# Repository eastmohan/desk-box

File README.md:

# desk-box
box on my desk with clock, timer/pomodoro timer, alarm clock, stop watch, maybe also make it a bluetooth speaker idk. havent decided if battery powered or plug in. i might also add charging ports for it to charge stuff like my phone. lamp too.

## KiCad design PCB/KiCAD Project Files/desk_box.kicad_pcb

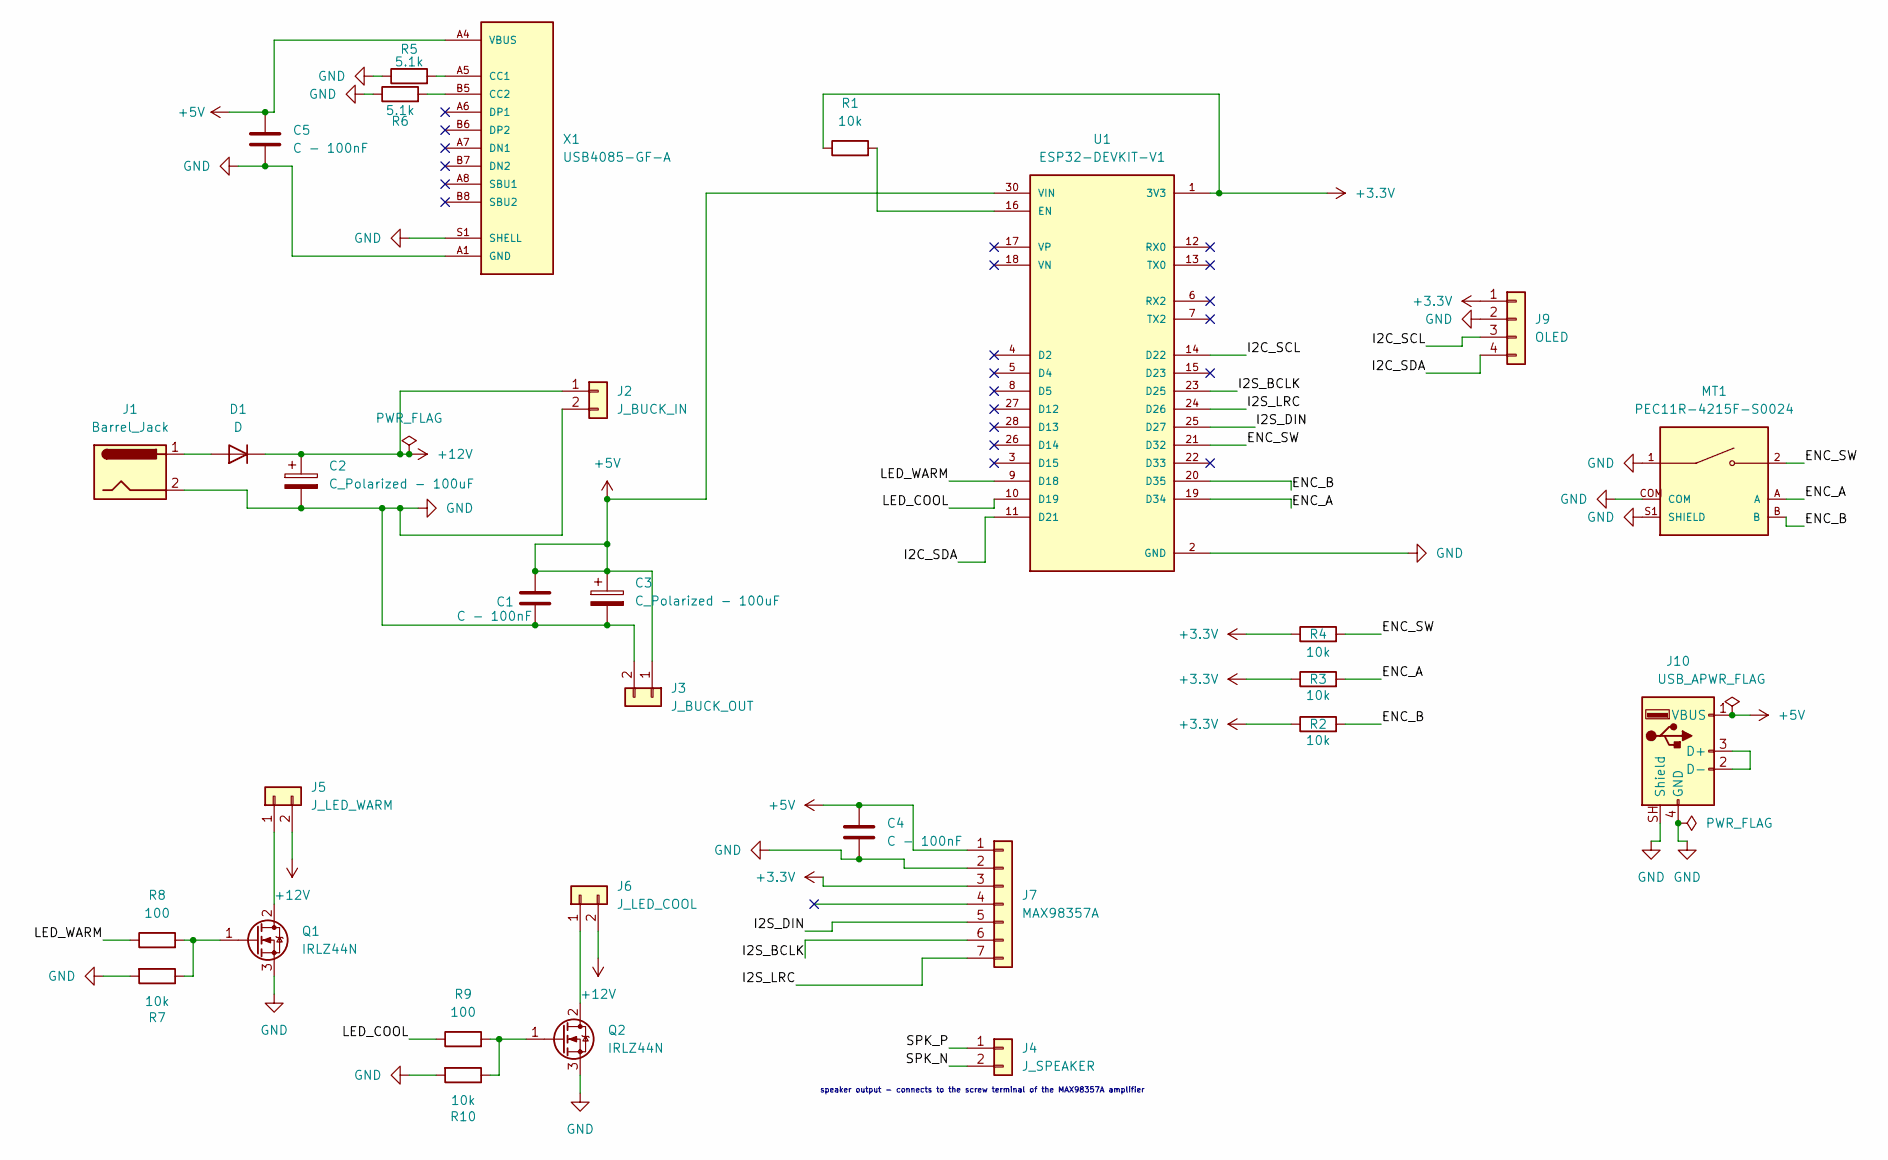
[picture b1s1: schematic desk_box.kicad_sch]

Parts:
C1, C4, C5: C - 100nF; C_Disc_D5.0mm_W2.5mm_P5.00mm
C2, C3: C_Polarized - 100uF; CP_Radial_D8.0mm_P3.50mm
D1: D; D_DO-41_SOD81_P10.16mm_Horizontal
J1: Barrel_Jack; PinHeader_1x02_P2.54mm_Vertical
J2: J_BUCK_IN; PinHeader_1x02_P2.54mm_Vertical
J3: J_BUCK_OUT; PinHeader_1x02_P2.54mm_Vertical
J4: J_SPEAKER; PinHeader_1x02_P2.54mm_Vertical
J5: J_LED_WARM; PinHeader_1x02_P2.54mm_Vertical
J6: J_LED_COOL; PinHeader_1x02_P2.54mm_Vertical
J7: MAX98357A; PinHeader_1x07_P2.54mm_Vertical
J9: OLED; PinHeader_1x04_P2.54mm_Vertical
J10: USB_A; USB_A_Molex_67643_Horizontal
MT1: PEC11R-4215F-S0024; XDCR_PEC11R-4215F-S0024; PARTREV Rev. 09/19
Q1, Q2: IRLZ44N; TO-220-3_Vertical
R1, R2, R3, R4, R7, R10: 10k; R_Axial_DIN0207_L6.3mm_D2.5mm_P10.16mm_Horizontal
R5, R6: 5.1k; R_Axial_DIN0207_L6.3mm_D2.5mm_P10.16mm_Horizontal
R8, R9: 100; R_Axial_DIN0207_L6.3mm_D2.5mm_P10.16mm_Horizontal
U1: ESP32-DEVKIT-V1; MODULE_ESP32_DEVKIT_V1; PARTREV N/A
X1: USB4085-GF-A; GCT_USB4085-GF-A_REVB

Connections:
+3.3V: J7.3, J9.1, R1.1, R2.1, R3.1, R4.1, U1.1 (3V3)
+5V: C1.1, C3.1, C4.1, C5.1, J3.1, J7.1, J10.1 (VBUS), U1.30 (VIN), X1.A4 (VBUS), X1.A9 (VBUS), X1.B4 (VBUS), X1.B9 (VBUS)
+12V: C2.1, D1.1 (K), J2.1, J5.2, J6.2
/ENC_A: MT1.A, R3.2, U1.19 (D34)
/ENC_B: MT1.B, R2.2, U1.20 (D35)
/ENC_SW: MT1.2, R4.2, U1.21 (D32)
/I2C_SCL: J9.3, U1.14 (D22)
/I2C_SDA: J9.4, U1.11 (D21)
/I2S_BCLK: J7.6, U1.23 (D25)
/I2S_DIN: J7.5, U1.25 (D27)
/I2S_LRC: J7.7, U1.24 (D26)
/LED_COOL: R9.1, U1.10 (D19)
/LED_WARM: R8.1, U1.9 (D18)
/SPK_N: J4.2
/SPK_P: J4.1
GND: C1.2, C2.2, C3.2, C4.2, C5.2, J1.2, J2.2, J3.2, J7.2, J9.2, J10.4 (GND), J10.SH (Shield), MT1.1, MT1.COM, MT1.S1 (SHIELD), MT1.S2 (SHIELD), Q1.3 (S), Q2.3 (S), R5.1, R6.1, R7.2, R10.2, U1.2 (GND), U1.29 (GND), X1.A1 (GND), X1.A12 (GND), X1.B1 (GND), X1.B12 (GND), X1.S1 (SHELL), X1.S2 (SHELL), X1.S3 (SHELL), X1.S4 (SHELL)
unnamed: D1.2 (A), J1.1
unnamed: J5.1, Q1.2 (D)
unnamed: J6.1, Q2.2 (D)
unnamed: J10.2 (D-), J10.3 (D+)
unnamed: Q1.1 (G), R7.1, R8.2
unnamed: Q2.1 (G), R9.2, R10.1
unnamed: R1.2, U1.16 (EN)
unnamed: R5.2, X1.A5 (CC1)
unnamed: R6.2, X1.B5 (CC2)

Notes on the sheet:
speaker output - connects to the screw terminal of the MAX98357A amplifier

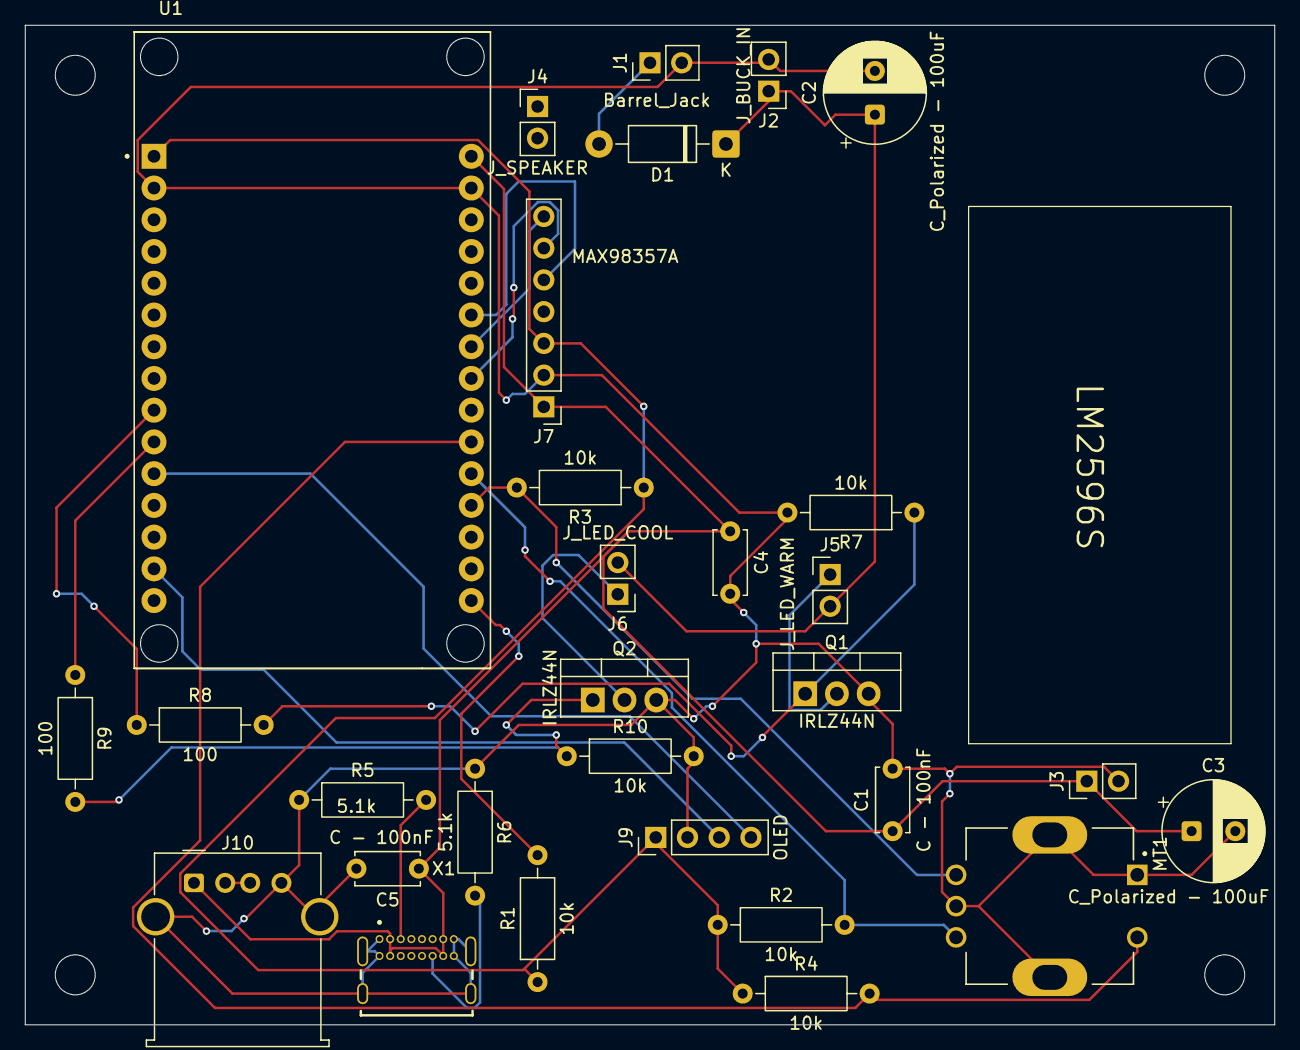
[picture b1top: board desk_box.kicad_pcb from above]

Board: 2 copper layers, 100.0 x 80.0 mm, 30 parts (0 on the bottom side), 23 nets.

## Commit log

2026-04-04 added hardware parts
2026-04-04 added more hardware cad files
2026-04-04 more hardware
2026-04-05 Schematic and PCB
2026-04-05 Gerber and drill files
2026-04-08 some firmware
